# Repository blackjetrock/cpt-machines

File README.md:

# CPT Machine information

The CPT Corporation made a few word processor machines in the 1970s and 80s. There is information here about specifically the:

4200
8000
8500

CPT 4200
========

This is a TTL (no processor) word processing tool that used a (modified) IBM Selectric for input and output. The 4200 console was a unit with a few keys and two tape decks. Text could be saved on the tapes, together with information such as names and addresses, these could be combined automatically later, creating a mail-merge facility.

CPT8000
=======
The 8000 is an 8080 based word processing system. It uses floppy drives for storage.

CPT8500
=======

The 8500 is an 8000 in a condensed form. The circuitry from the 8000 has been squashed down onto a smaller number of PCBs.

8000 Re-creation
================

I have a set of CPT8500 PCBs, but nothing else. I'm planning on recreating the parts I need in order to get the boards running again.

The backplane is the first part needed, this has been designed and is untested:

I've also designed a diagnostic/debug card (untested) which is a Pico on a bus:

Acknowledgements
================

Thanks to Adrian at Binary Dinosaurs, who has helped a lot with data from his real CPT machine.
Rich, who used to work at CPT has generously scanned and supplied the chematics of the 8000, without which these projects would not have started.

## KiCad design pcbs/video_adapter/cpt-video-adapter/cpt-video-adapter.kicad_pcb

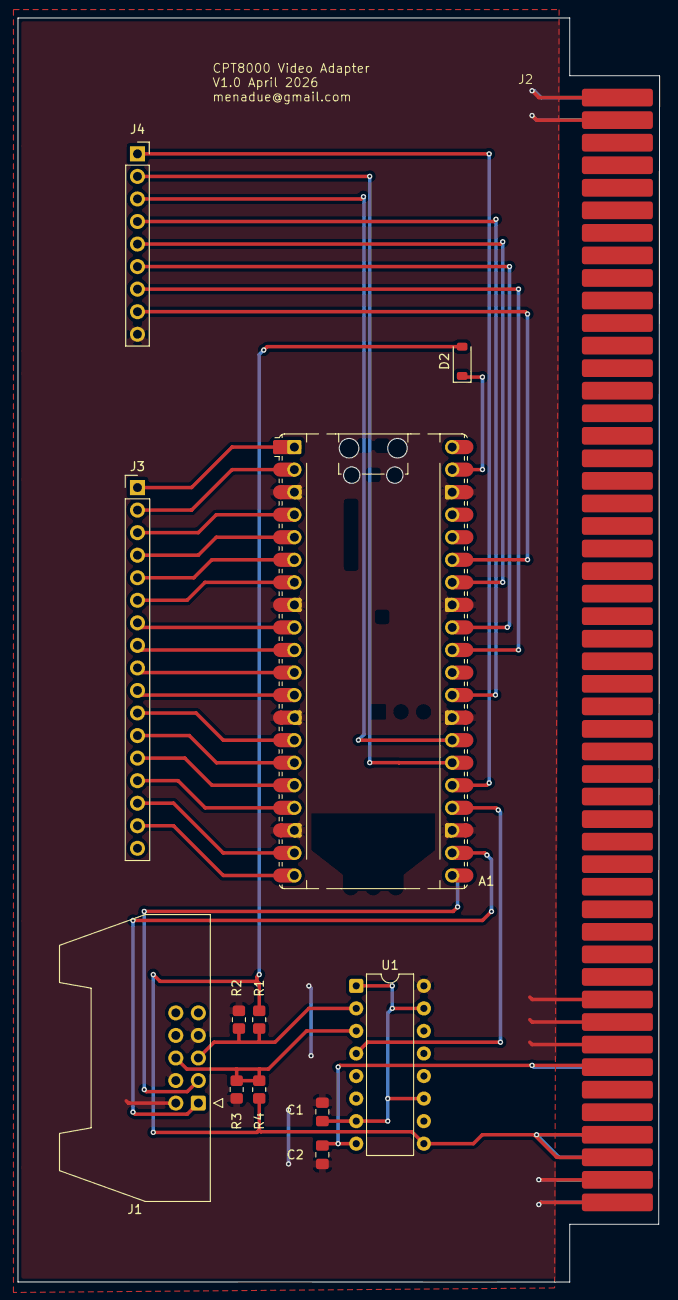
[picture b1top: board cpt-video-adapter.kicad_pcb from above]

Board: 2 copper layers, 72.3 x 142.4 mm, 13 parts (0 on the bottom side), 34 nets.

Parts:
A1: RaspberryPi_Pico; RaspberryPi_Pico_Common_Unspecified
C1, C2: C_Small; C_0805_2012Metric_Pad1.18x1.45mm_HandSolder
D2: D_Schottky; D_SOD-123
J1: Conn_02x05_Odd_Even; IDC-Header_2x05_P2.54mm_Latch_Horizontal
J2: cpt-backplane_100; cpt-card-edge-100
J3: Conn_01x17_Pin; PinHeader_1x17_P2.54mm_Vertical
J4: Conn_01x09; PinSocket_1x09_P2.54mm_Vertical
R1, R2, R3, R4: R_Small; R_0805_2012Metric_Pad1.20x1.40mm_HandSolder
U1: mc10125; DIP-16_W7.62mm

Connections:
+5V: D2.2 (A), J2.93 (+5V), J2.94 (+5V), J2.95 (+5V), J2.96 (+5V), R1.1, R3.1, U1.9 (VCC)
-5V: C2.1, J2.87 (-5V), J2.88 (-5V), U1.8 (VEE)
GND: A1.3 (GND), A1.8 (GND), A1.13 (GND), A1.18 (GND), A1.23 (GND), A1.28 (GND), A1.33 (AGND), A1.38 (GND), C1.2, C2.2, J1.2, J1.4, J1.7, J2.1 (GND), J2.2 (GND), J2.3 (GND), J2.4 (GND), J2.82 (GND), J2.84 (GND), J2.86 (GND), J2.97 (GND), J2.98 (GND), J2.99 (GND), J2.100 (GND), J4.9, R2.2, R4.2, U1.16 (GND)
HSYNC: A1.22 (GPIO17), J1.1
unnamed: A1.35 (ADC_VREF), J4.8
unnamed: A1.1 (GPIO0), J3.1
unnamed: A1.2 (GPIO1), J3.2
unnamed: A1.4 (GPIO2), J3.3
unnamed: A1.5 (GPIO3), J3.4
unnamed: A1.6 (GPIO4), J3.5
unnamed: A1.7 (GPIO5), J3.6
unnamed: A1.9 (GPIO6), J3.7
unnamed: A1.10 (GPIO7), J3.8
unnamed: A1.11 (GPIO8), J3.9
unnamed: A1.12 (GPIO9), J3.10
unnamed: A1.14 (GPIO10), J3.11
unnamed: A1.15 (GPIO11), J3.12
unnamed: A1.16 (GPIO12), J3.13
unnamed: A1.17 (GPIO13), J3.14
unnamed: A1.19 (GPIO14), J3.15
unnamed: A1.20 (GPIO15), J3.16
unnamed: A1.25 (GPIO19), J4.1
unnamed: A1.26 (GPIO20), J4.2
unnamed: A1.27 (GPIO21), J4.3
unnamed: A1.29 (GPIO22), J4.4
unnamed: A1.31 (GPIO26_ADC0), J4.7
unnamed: A1.32 (GPIO27_ADC1), J4.6
unnamed: A1.34 (GPIO28_ADC2), J4.5
unnamed: A1.39 (VSYS), D2.1 (K)
unnamed: C1.1, U1.1 (VBB), U1.7 (BIN), U1.11 (CIN), U1.15 (DIN)
VIDEO_N: J1.5, R1.2, R2.1, U1.2 (/AIN)
VIDEO_P: J1.6, R3.2, R4.1, U1.3 (AIN)
VIDEO_TTL: A1.24 (GPIO18), U1.4 (AOUT)
VSYNC: A1.21 (GPIO16), J1.3

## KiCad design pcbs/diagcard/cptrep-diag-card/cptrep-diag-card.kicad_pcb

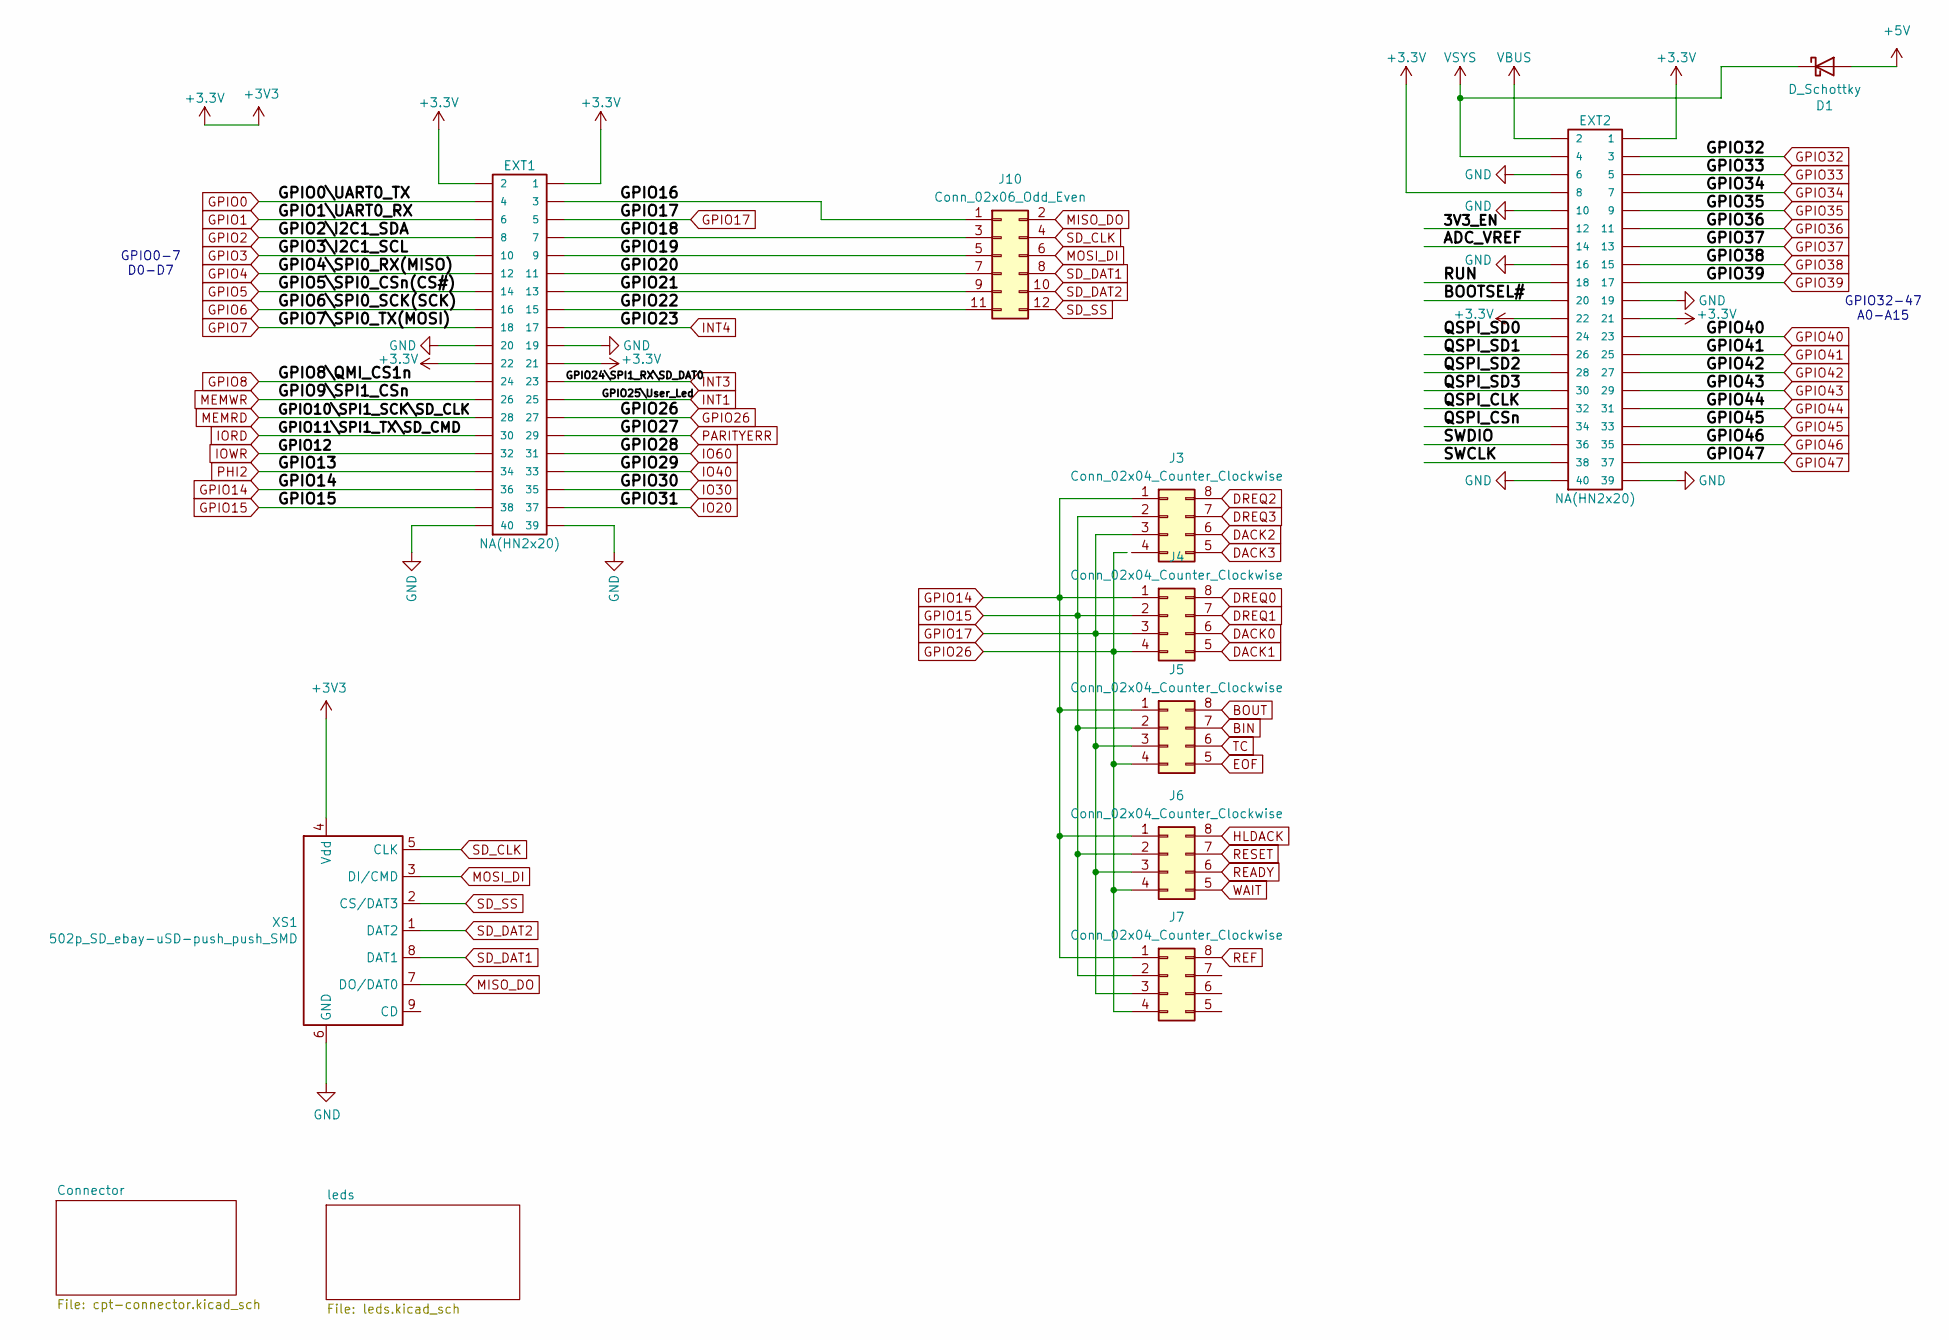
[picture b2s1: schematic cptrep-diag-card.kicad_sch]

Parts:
D1: D_Schottky; D_SOD-123
EXT1, EXT2: NA(HN2x20); PinSocket_2x20_P2.54mm_Vertical
J3, J4, J5, J6, J7: Conn_02x04_Counter_Clockwise; PinHeader_2x04_P2.54mm_Vertical
J10: Conn_02x06_Odd_Even; PinHeader_2x06_P2.54mm_Vertical
XS1: 502p_SD_ebay-uSD-push_push_SMD; Conn_uSDcard

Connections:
+3.3V: EXT1.1, EXT1.2, EXT1.21, EXT1.22, EXT2.1, EXT2.8, EXT2.21, EXT2.22, XS1.4 (Vdd)
+5V: D1.2 (A); also elsewhere on the board
/3V3_EN: EXT2.12
/ADC_VREF: EXT2.14
/BOOTSEL#: EXT2.20
/GPIO16: EXT1.3, J10.1
/GPIO18: EXT1.7, J10.3
/GPIO19: EXT1.9, J10.5
/GPIO20: EXT1.11, J10.7
/GPIO21: EXT1.13, J10.9
/GPIO22: EXT1.15, J10.11
/QSPI_CLK: EXT2.32
/QSPI_CSn: EXT2.34
/QSPI_SD0: EXT2.24
/QSPI_SD1: EXT2.26
/QSPI_SD2: EXT2.28
/QSPI_SD3: EXT2.30
/RUN: EXT2.18
/SWCLK: EXT2.38
/SWDIO: EXT2.36
BIN: J5.7; also elsewhere on the board
BOUT: J5.8; also elsewhere on the board
DACK0: J4.6; also elsewhere on the board
DACK1: J4.5; also elsewhere on the board
DACK2: J3.6; also elsewhere on the board
DACK3: J3.5; also elsewhere on the board
DREQ0: J4.8; also elsewhere on the board
DREQ1: J4.7; also elsewhere on the board
DREQ2: J3.8; also elsewhere on the board
DREQ3: J3.7; also elsewhere on the board
EOF: J5.5; also elsewhere on the board
GND: EXT1.19, EXT1.20, EXT1.39, EXT1.40, EXT2.6, EXT2.10, EXT2.16, EXT2.19, EXT2.39, EXT2.40, XS1.6 (GND); also elsewhere on the board
GPIO0: EXT1.4; also elsewhere on the board
GPIO1: EXT1.6; also elsewhere on the board
GPIO2: EXT1.8; also elsewhere on the board
GPIO3: EXT1.10; also elsewhere on the board
GPIO4: EXT1.12; also elsewhere on the board
GPIO5: EXT1.14; also elsewhere on the board
GPIO6: EXT1.16; also elsewhere on the board
GPIO7: EXT1.18; also elsewhere on the board
GPIO8: EXT1.24; also elsewhere on the board
GPIO14: EXT1.36, J3.1, J4.1, J5.1, J6.1, J7.1; also elsewhere on the board
GPIO15: EXT1.38, J3.2, J4.2, J5.2, J6.2, J7.2; also elsewhere on the board
GPIO17: EXT1.5, J3.3, J4.3, J5.3, J6.3, J7.3; also elsewhere on the board
GPIO26: EXT1.27, J4.4, J5.4, J6.4, J7.4; also elsewhere on the board
GPIO32: EXT2.3; also elsewhere on the board
GPIO33: EXT2.5; also elsewhere on the board
GPIO34: EXT2.7; also elsewhere on the board
GPIO35: EXT2.9; also elsewhere on the board
GPIO36: EXT2.11; also elsewhere on the board
GPIO37: EXT2.13; also elsewhere on the board
GPIO38: EXT2.15; also elsewhere on the board
GPIO39: EXT2.17; also elsewhere on the board
GPIO40: EXT2.23; also elsewhere on the board
GPIO41: EXT2.25; also elsewhere on the board
GPIO42: EXT2.27; also elsewhere on the board
GPIO43: EXT2.29; also elsewhere on the board
GPIO44: EXT2.31; also elsewhere on the board
GPIO45: EXT2.33; also elsewhere on the board
GPIO46: EXT2.35; also elsewhere on the board
GPIO47: EXT2.37; also elsewhere on the board
HLDACK: J6.8; also elsewhere on the board
INT1: EXT1.25; also elsewhere on the board
INT3: EXT1.23; also elsewhere on the board
INT4: EXT1.17; also elsewhere on the board
IO20: EXT1.37; also elsewhere on the board
IO30: EXT1.35; also elsewhere on the board
IO40: EXT1.33; also elsewhere on the board
IO60: EXT1.31; also elsewhere on the board
IORD: EXT1.30; also elsewhere on the board
IOWR: EXT1.32; also elsewhere on the board
MEMRD: EXT1.28; also elsewhere on the board
MEMWR: EXT1.26; also elsewhere on the board
MISO_DO: J10.2, XS1.7 (DO/DAT0)
MOSI_DI: J10.6, XS1.3 (DI/CMD)
PARITYERR: EXT1.29; also elsewhere on the board
PHI2: EXT1.34; also elsewhere on the board
READY: J6.6; also elsewhere on the board
REF: J7.8; also elsewhere on the board
RESET: J6.7; also elsewhere on the board
SD_CLK: J10.4, XS1.5 (CLK)
SD_DAT1: J10.8, XS1.8 (DAT1)
SD_DAT2: J10.10, XS1.1 (DAT2)
SD_SS: J10.12, XS1.2 (CS/DAT3)
TC: J5.6; also elsewhere on the board
VBUS: EXT2.2
VSYS: D1.1 (K), EXT2.4
WAIT: J6.5; also elsewhere on the board

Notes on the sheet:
GPIO32-47 A0-A15
GPIO0-7 D0-D7

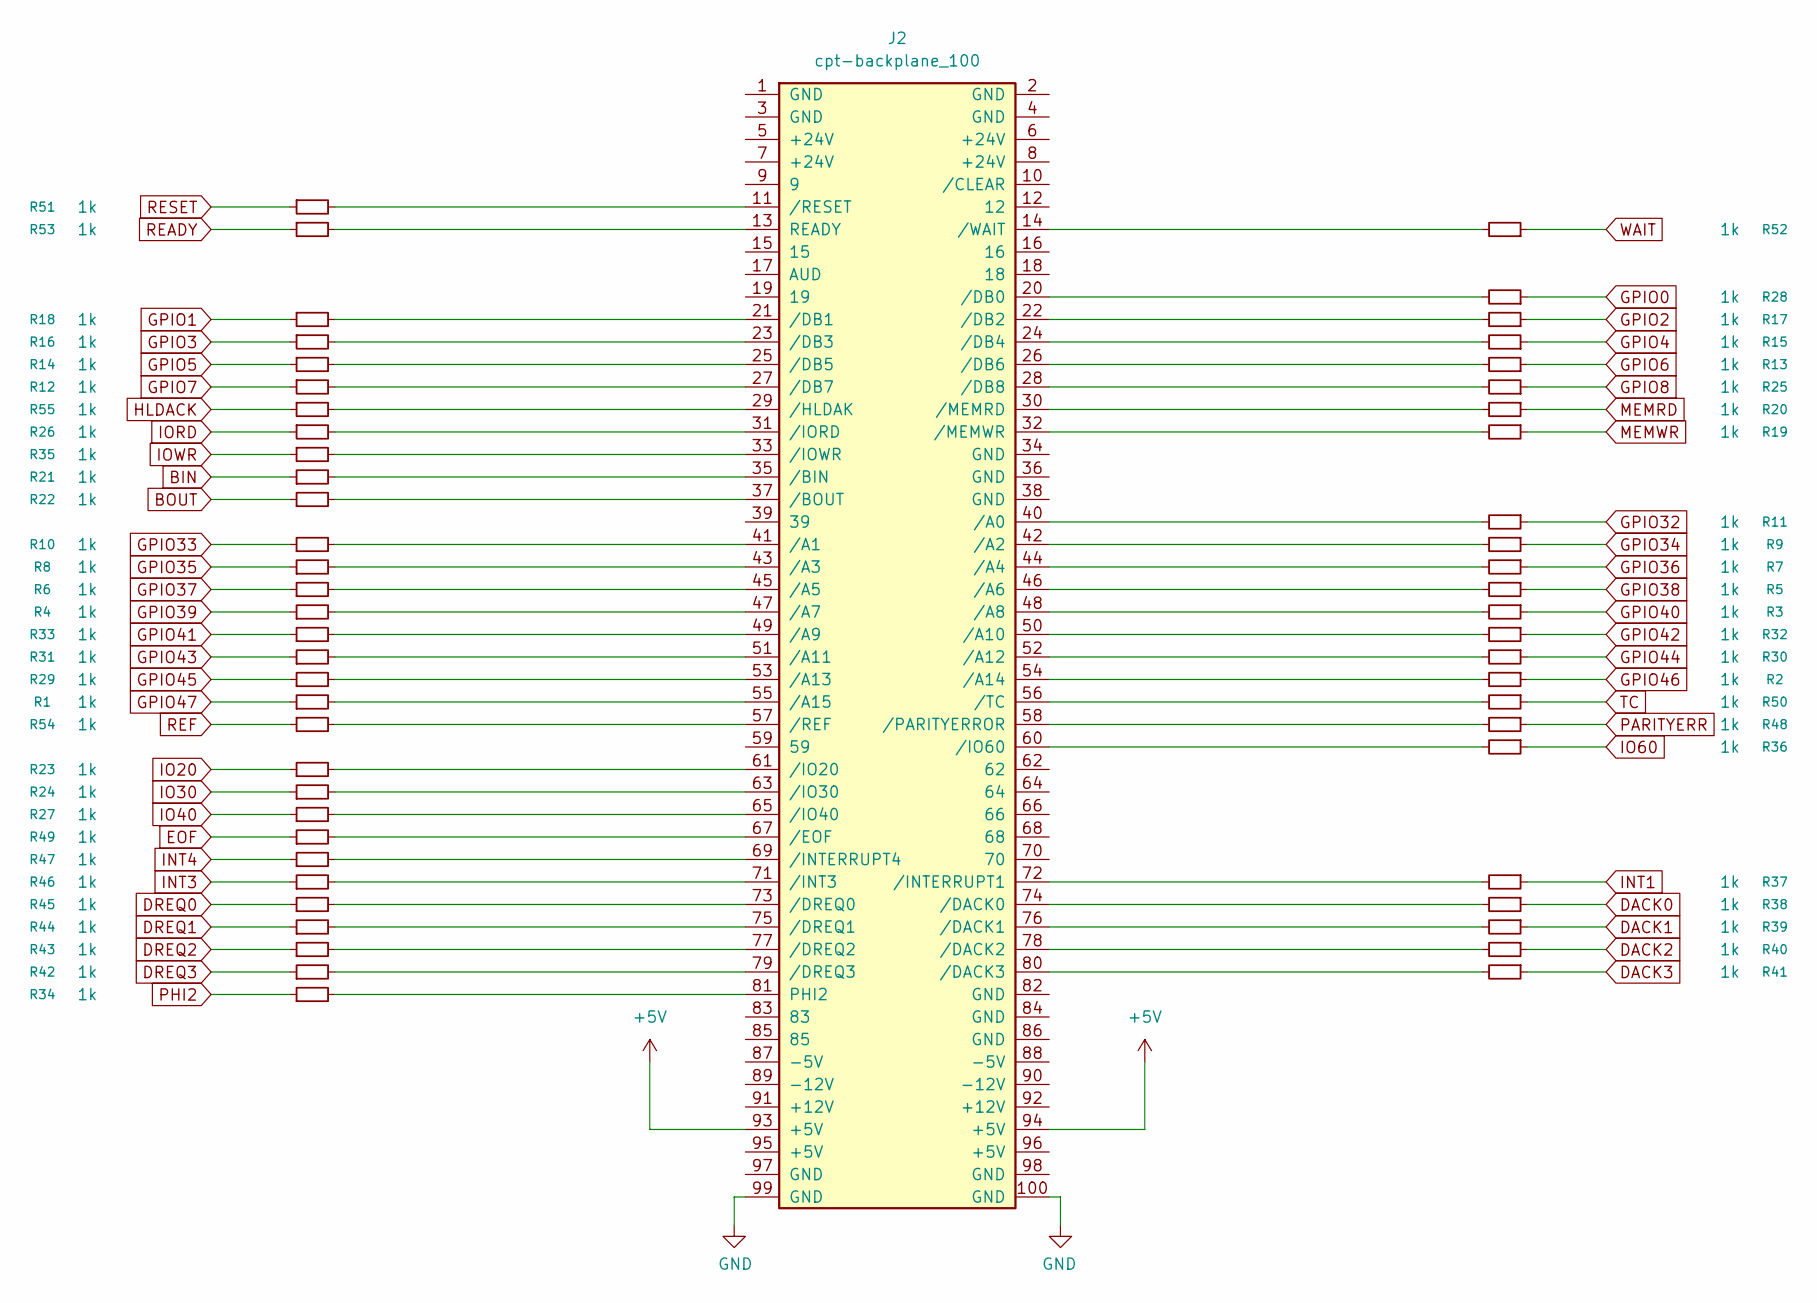
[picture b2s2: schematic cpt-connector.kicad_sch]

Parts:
J2: cpt-backplane_100; cpt-card-edge-100
R1, R2, R3, R4, R5, R6, R7, R8, R9, R10, R11, R12, R13, R14, R15, R16, R17, R18, R19, R20, R21, R22, R23, R24, R25, R26, R27, R28, R29, R30, R31, R32, R33, R34, R35, R36, R37, R38, R39, R40, R41, R42, R43, R44, R45, R46, R47, R48, R49, R50, R51, R52, R53, R54, R55: 1k; R_0805_2012Metric_Pad1.20x1.40mm_HandSolder

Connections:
+5V: J2.93 (+5V), J2.94 (+5V); also elsewhere on the board
BIN: R21.1; also elsewhere on the board
BOUT: R22.1; also elsewhere on the board
DACK0: R38.1; also elsewhere on the board
DACK1: R39.1; also elsewhere on the board
DACK2: R40.1; also elsewhere on the board
DACK3: R41.1; also elsewhere on the board
DREQ0: R45.1; also elsewhere on the board
DREQ1: R44.1; also elsewhere on the board
DREQ2: R43.1; also elsewhere on the board
DREQ3: R42.1; also elsewhere on the board
EOF: R49.1; also elsewhere on the board
GND: J2.1 (GND), J2.2 (GND), J2.3 (GND), J2.4 (GND), J2.99 (GND), J2.100 (GND); also elsewhere on the board
GPIO0: R28.1; also elsewhere on the board
GPIO1: R18.1; also elsewhere on the board
GPIO2: R17.1; also elsewhere on the board
GPIO3: R16.1; also elsewhere on the board
GPIO4: R15.1; also elsewhere on the board
GPIO5: R14.1; also elsewhere on the board
GPIO6: R13.1; also elsewhere on the board
GPIO7: R12.1; also elsewhere on the board
GPIO8: R25.1; also elsewhere on the board
GPIO32: R11.1; also elsewhere on the board
GPIO33: R10.1; also elsewhere on the board
GPIO34: R9.1; also elsewhere on the board
GPIO35: R8.1; also elsewhere on the board
GPIO36: R7.1; also elsewhere on the board
GPIO37: R6.1; also elsewhere on the board
GPIO38: R5.1; also elsewhere on the board
GPIO39: R4.1; also elsewhere on the board
GPIO40: R3.1; also elsewhere on the board
GPIO41: R33.1; also elsewhere on the board
GPIO42: R32.1; also elsewhere on the board
GPIO43: R31.1; also elsewhere on the board
GPIO44: R30.1; also elsewhere on the board
GPIO45: R29.1; also elsewhere on the board
GPIO46: R2.1; also elsewhere on the board
GPIO47: R1.1; also elsewhere on the board
HLDACK: R55.1; also elsewhere on the board
INT1: R37.1; also elsewhere on the board
INT3: R46.1; also elsewhere on the board
INT4: R47.1; also elsewhere on the board
IO20: R23.1; also elsewhere on the board
IO30: R24.1; also elsewhere on the board
IO40: R27.1; also elsewhere on the board
IO60: R36.1; also elsewhere on the board
IORD: R26.1; also elsewhere on the board
IOWR: R35.1; also elsewhere on the board
MEMRD: R20.1; also elsewhere on the board
MEMWR: R19.1; also elsewhere on the board
unnamed: J2.81 (PHI2), R34.2
unnamed: J2.13 (READY), R53.2
unnamed: J2.40 (/A0), R11.2
unnamed: J2.41 (/A1), R10.2
unnamed: J2.42 (/A2), R9.2
unnamed: J2.43 (/A3), R8.2
unnamed: J2.44 (/A4), R7.2
unnamed: J2.45 (/A5), R6.2
unnamed: J2.46 (/A6), R5.2
unnamed: J2.47 (/A7), R4.2
unnamed: J2.48 (/A8), R3.2
unnamed: J2.49 (/A9), R33.2
unnamed: J2.50 (/A10), R32.2
unnamed: J2.51 (/A11), R31.2
unnamed: J2.52 (/A12), R30.2
unnamed: J2.53 (/A13), R29.2
unnamed: J2.54 (/A14), R2.2
unnamed: J2.55 (/A15), R1.2
unnamed: J2.35 (/BIN), R21.2
unnamed: J2.37 (/BOUT), R22.2
unnamed: J2.74 (/DACK0), R38.2
unnamed: J2.76 (/DACK1), R39.2
unnamed: J2.78 (/DACK2), R40.2
unnamed: J2.80 (/DACK3), R41.2
unnamed: J2.20 (/DB0), R28.2
unnamed: J2.21 (/DB1), R18.2
unnamed: J2.22 (/DB2), R17.2
unnamed: J2.23 (/DB3), R16.2
unnamed: J2.24 (/DB4), R15.2
unnamed: J2.25 (/DB5), R14.2
unnamed: J2.26 (/DB6), R13.2
unnamed: J2.27 (/DB7), R12.2
unnamed: J2.28 (/DB8), R25.2
unnamed: J2.73 (/DREQ0), R45.2
unnamed: J2.75 (/DREQ1), R44.2
unnamed: J2.77 (/DREQ2), R43.2
unnamed: J2.79 (/DREQ3), R42.2
unnamed: J2.67 (/EOF), R49.2
unnamed: J2.29 (/HLDAK), R55.2
unnamed: J2.71 (/INT3), R46.2
unnamed: J2.72 (/INTERRUPT1), R37.2
unnamed: J2.69 (/INTERRUPT4), R47.2
unnamed: J2.61 (/IO20), R23.2
unnamed: J2.63 (/IO30), R24.2
unnamed: J2.65 (/IO40), R27.2
unnamed: J2.60 (/IO60), R36.2
unnamed: J2.31 (/IORD), R26.2
unnamed: J2.33 (/IOWR), R35.2
unnamed: J2.30 (/MEMRD), R20.2
unnamed: J2.32 (/MEMWR), R19.2
unnamed: J2.58 (/PARITYERROR), R48.2
unnamed: J2.57 (/REF), R54.2
unnamed: J2.11 (/RESET), R51.2
unnamed: J2.56 (/TC), R50.2
unnamed: J2.14 (/WAIT), R52.2
PARITYERR: R48.1; also elsewhere on the board
PHI2: R34.1; also elsewhere on the board
READY: R53.1; also elsewhere on the board
REF: R54.1; also elsewhere on the board
RESET: R51.1; also elsewhere on the board
TC: R50.1; also elsewhere on the board
WAIT: R52.1; also elsewhere on the board

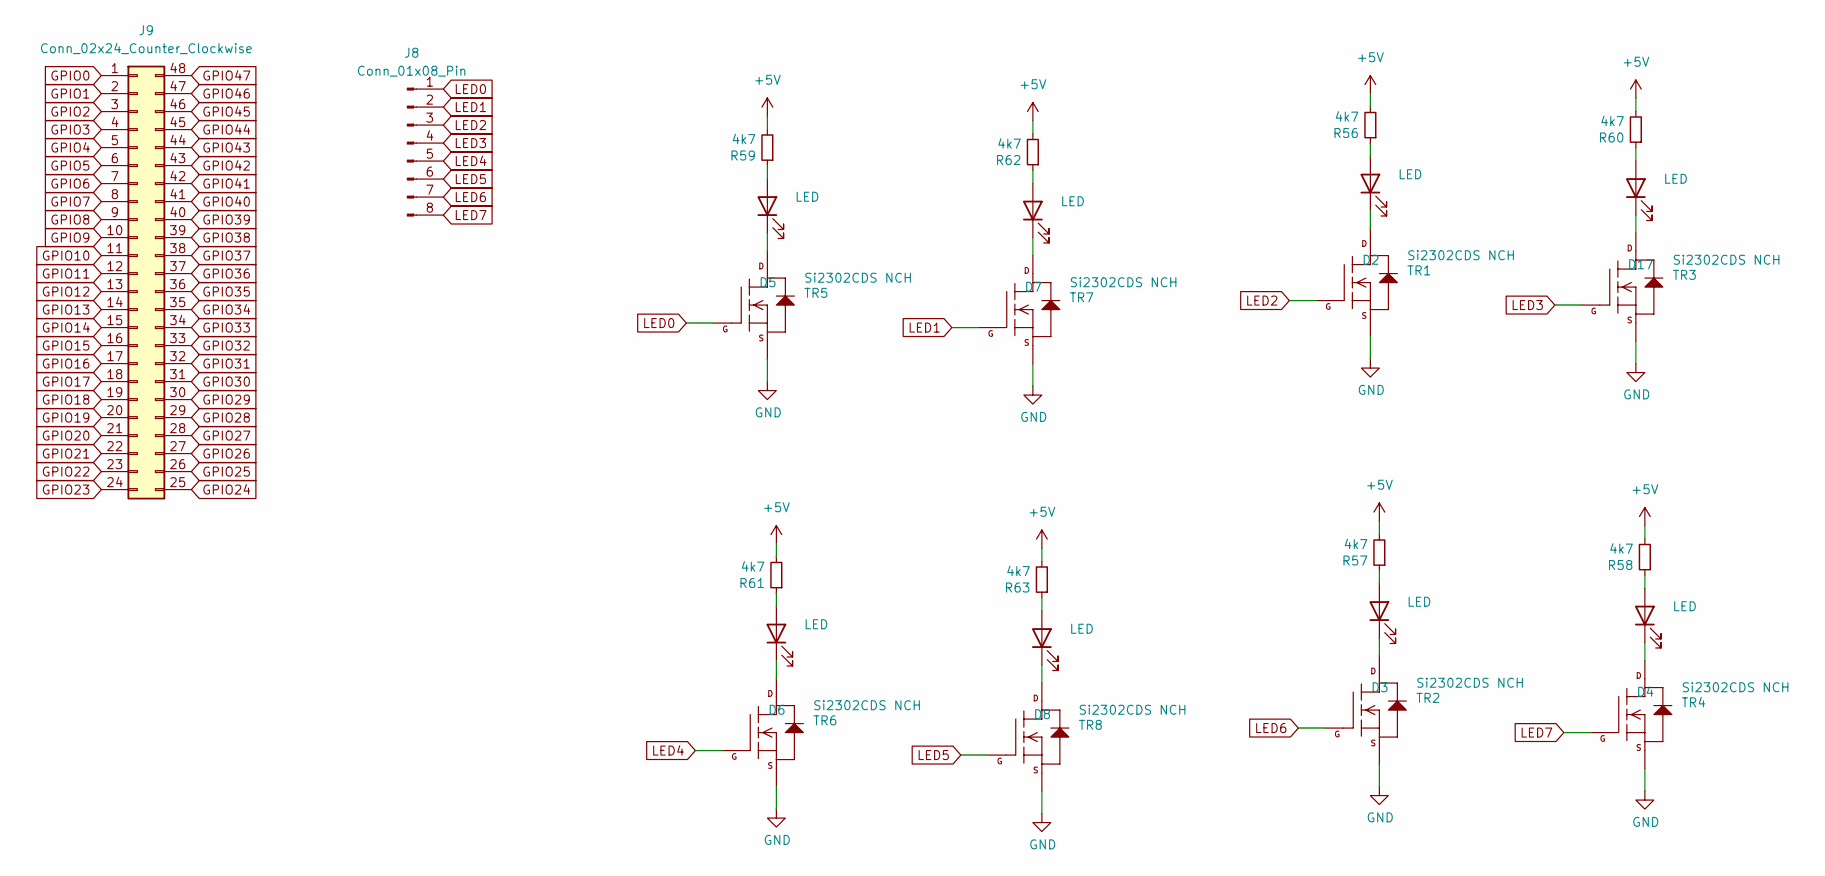
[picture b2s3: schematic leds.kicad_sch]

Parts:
D2, D3, D4, D5, D6, D7, D8, D17: LED; LED_0805_2012Metric
J8: Conn_01x08_Pin; PinHeader_1x08_P2.54mm_Vertical
J9: Conn_02x24_Counter_Clockwise; PinHeader_2x24_P2.54mm_Vertical
R56, R57, R58, R59, R60, R61, R62, R63: 4k7; R_0805_2012Metric
TR1, TR2, TR3, TR4, TR5, TR6, TR7, TR8: Si2302CDS NCH; SOT-23

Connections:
+5V: R56.2, R57.2, R58.2, R59.2, R60.2, R61.2, R62.2, R63.2; also elsewhere on the board
GND: TR1.2 (S), TR2.2 (S), TR3.2 (S), TR4.2 (S), TR5.2 (S), TR6.2 (S), TR7.2 (S), TR8.2 (S); also elsewhere on the board
GPIO0: J9.1; also elsewhere on the board
GPIO1: J9.2; also elsewhere on the board
GPIO2: J9.3; also elsewhere on the board
GPIO3: J9.4; also elsewhere on the board
GPIO4: J9.5; also elsewhere on the board
GPIO5: J9.6; also elsewhere on the board
GPIO6: J9.7; also elsewhere on the board
GPIO7: J9.8; also elsewhere on the board
GPIO8: J9.9; also elsewhere on the board
GPIO9: J9.10
GPIO10: J9.11
GPIO11: J9.12
GPIO12: J9.13
GPIO13: J9.14
GPIO14: J9.15; also elsewhere on the board
GPIO15: J9.16; also elsewhere on the board
GPIO16: J9.17
GPIO17: J9.18; also elsewhere on the board
GPIO18: J9.19
GPIO19: J9.20
GPIO20: J9.21
GPIO21: J9.22
GPIO22: J9.23
GPIO23: J9.24
GPIO24: J9.25
GPIO25: J9.26
GPIO26: J9.27; also elsewhere on the board
GPIO27: J9.28
GPIO28: J9.29
GPIO29: J9.30
GPIO30: J9.31
GPIO31: J9.32
GPIO32: J9.33; also elsewhere on the board
GPIO33: J9.34; also elsewhere on the board
GPIO34: J9.35; also elsewhere on the board
GPIO35: J9.36; also elsewhere on the board
GPIO36: J9.37; also elsewhere on the board
GPIO37: J9.38; also elsewhere on the board
GPIO38: J9.39; also elsewhere on the board
GPIO39: J9.40; also elsewhere on the board
GPIO40: J9.41; also elsewhere on the board
GPIO41: J9.42; also elsewhere on the board
GPIO42: J9.43; also elsewhere on the board
GPIO43: J9.44; also elsewhere on the board
GPIO44: J9.45; also elsewhere on the board
GPIO45: J9.46; also elsewhere on the board
GPIO46: J9.47; also elsewhere on the board
GPIO47: J9.48; also elsewhere on the board
LED0: J8.1, TR5.1 (G)
LED1: J8.2, TR7.1 (G)
LED2: J8.3, TR1.1 (G)
LED3: J8.4, TR3.1 (G)
LED4: J8.5, TR6.1 (G)
LED5: J8.6, TR8.1 (G)
LED6: J8.7, TR2.1 (G)
LED7: J8.8, TR4.1 (G)
unnamed: D2.2 (A), R56.1
unnamed: D2.1 (K), TR1.3 (D)
unnamed: D3.2 (A), R57.1
unnamed: D3.1 (K), TR2.3 (D)
unnamed: D4.2 (A), R58.1
unnamed: D4.1 (K), TR4.3 (D)
unnamed: D5.2 (A), R59.1
unnamed: D5.1 (K), TR5.3 (D)
unnamed: D6.2 (A), R61.1
unnamed: D6.1 (K), TR6.3 (D)
unnamed: D7.2 (A), R62.1
unnamed: D7.1 (K), TR7.3 (D)
unnamed: D8.2 (A), R63.1
unnamed: D8.1 (K), TR8.3 (D)
unnamed: D17.2 (A), R60.1
unnamed: D17.1 (K), TR3.3 (D)

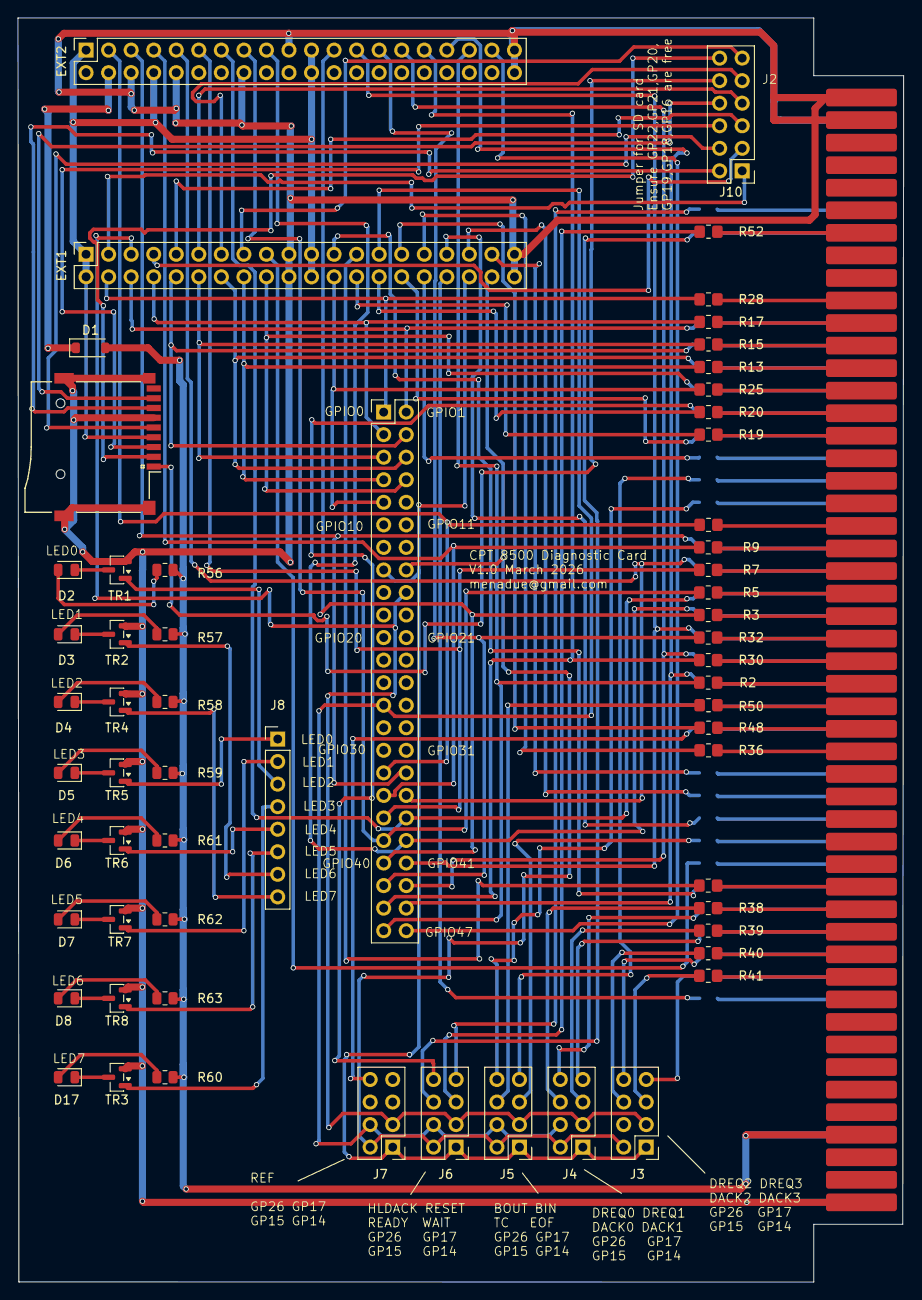
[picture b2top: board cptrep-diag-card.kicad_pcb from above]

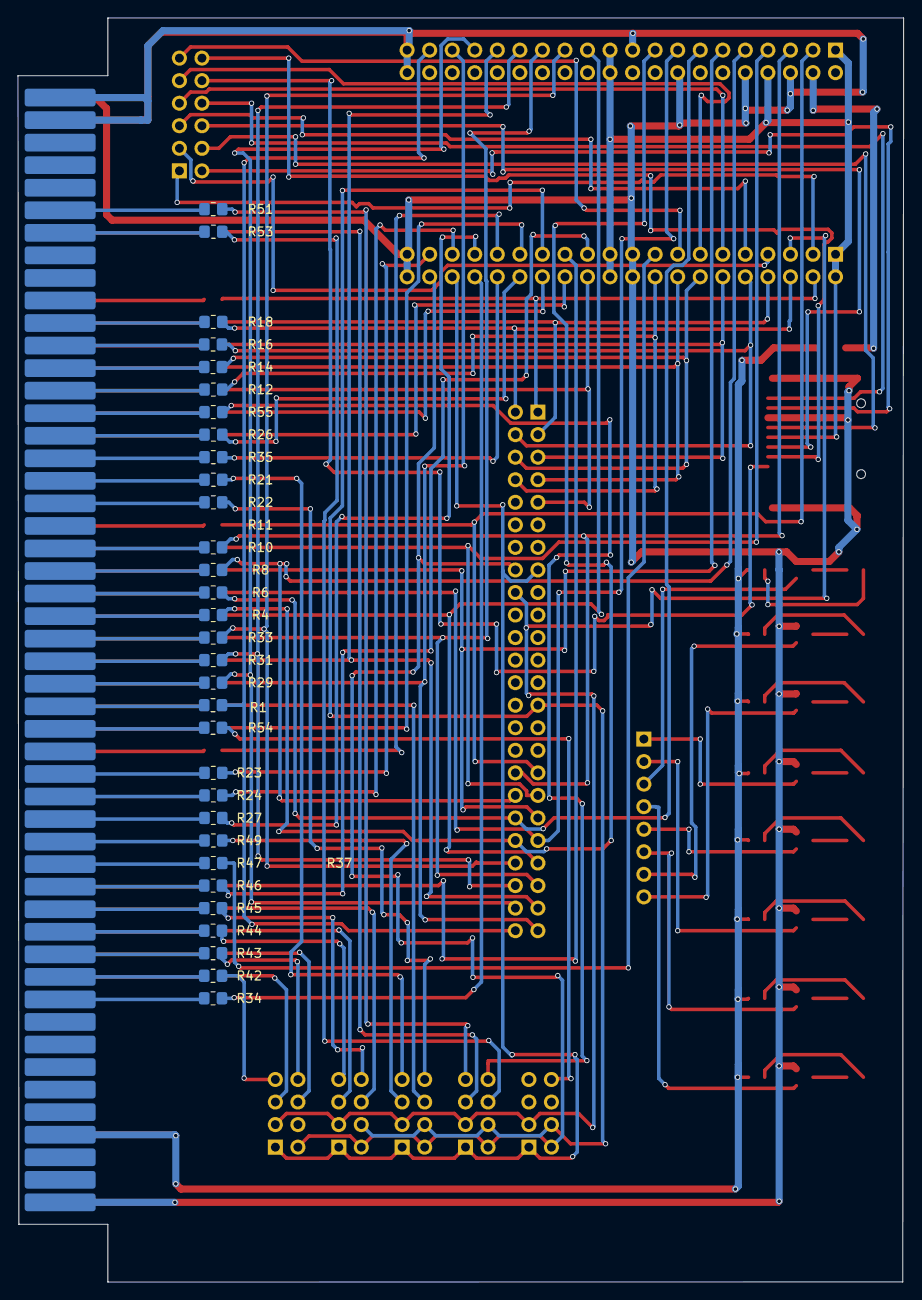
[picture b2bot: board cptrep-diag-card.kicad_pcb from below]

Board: 2 copper layers, 99.8 x 142.4 mm, 92 parts (31 on the bottom side), 154 nets.

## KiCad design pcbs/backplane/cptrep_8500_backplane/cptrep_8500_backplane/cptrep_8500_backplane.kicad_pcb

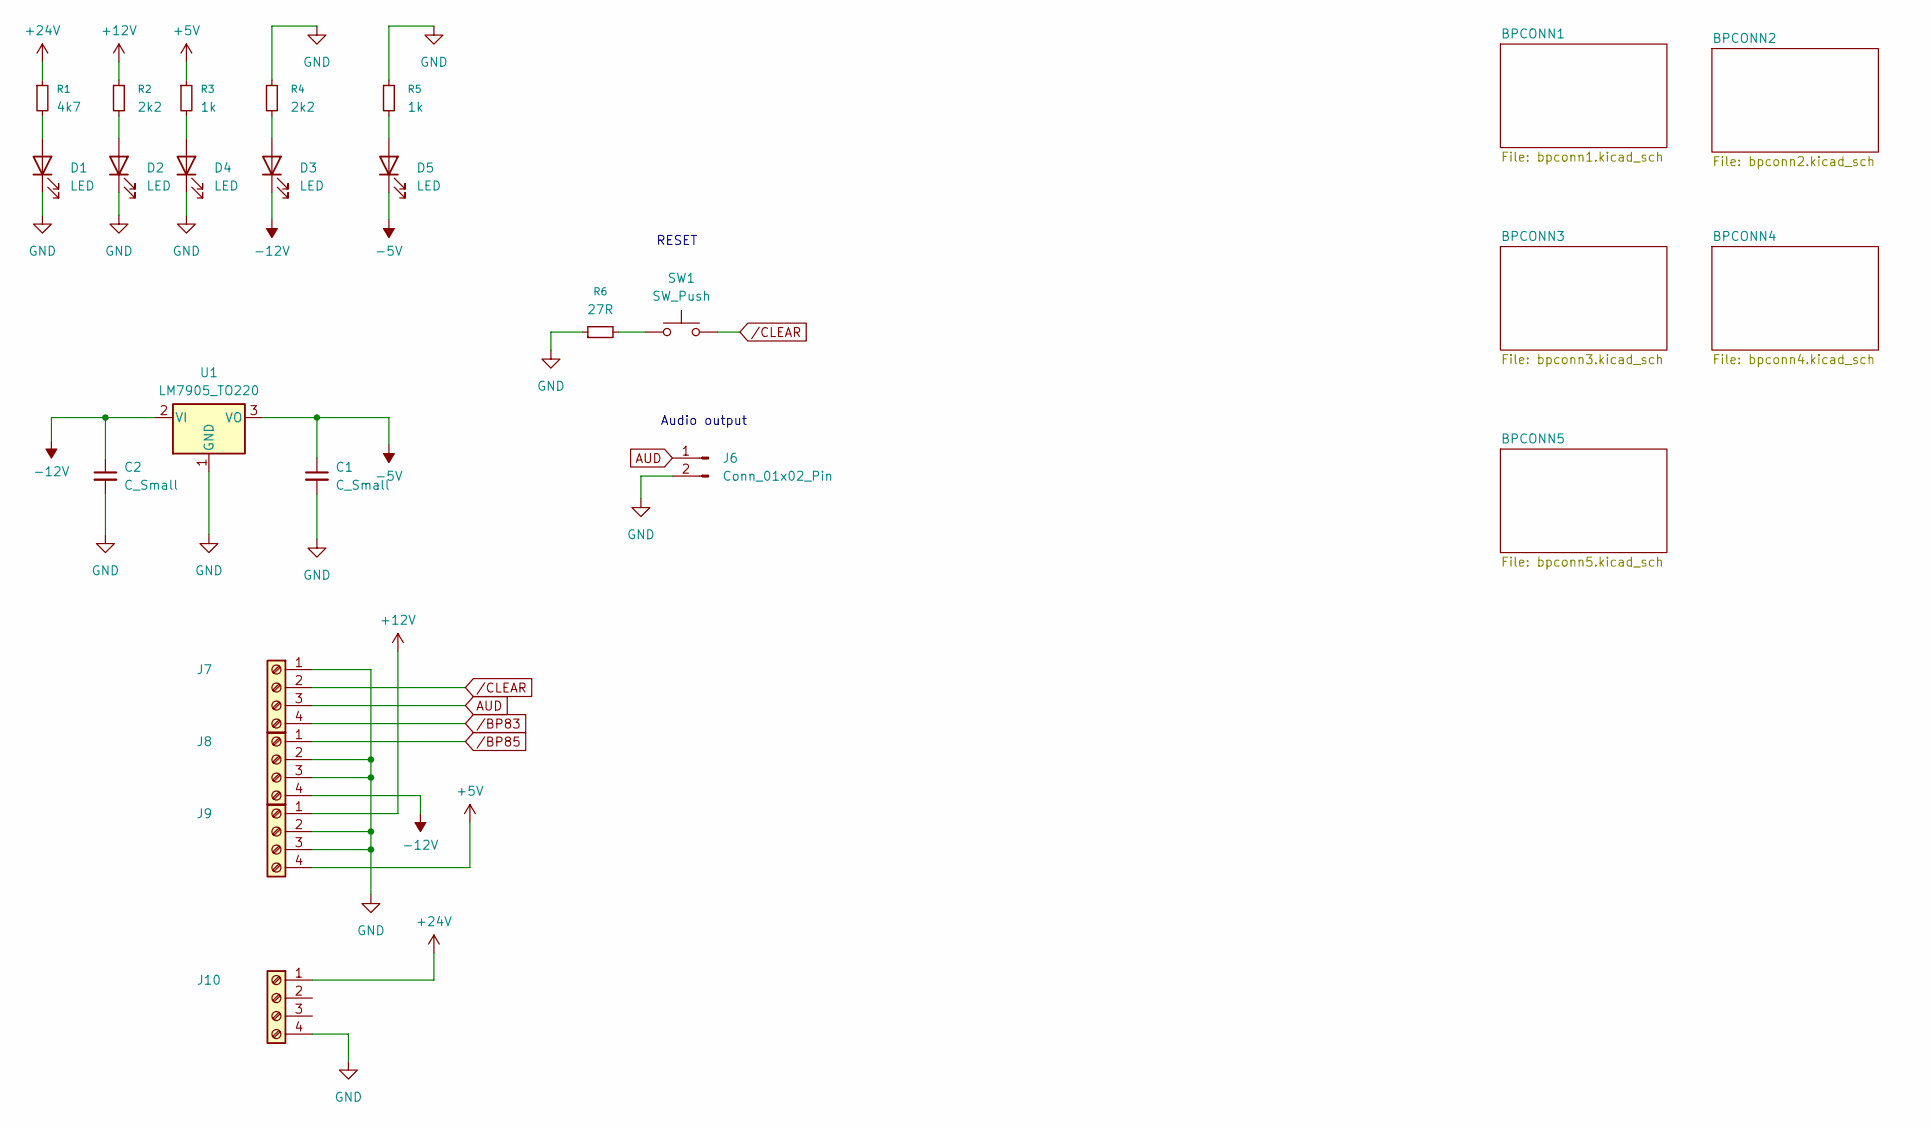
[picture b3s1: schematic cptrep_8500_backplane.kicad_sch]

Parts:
C1, C2: C_Small; C_0805_2012Metric_Pad1.18x1.45mm_HandSolder
D1, D2, D3, D4, D5: LED; LED_0805_2012Metric_Pad1.15x1.40mm_HandSolder
J6: Conn_01x02_Pin; PinSocket_1x02_P2.54mm_Vertical
J7, J8, J9, J10: Screw_Terminal_01x04; TerminalBlock_Phoenix_MKDS-1,5-4_1x04_P5.00mm_Horizontal
R1: 4k7; R_0805_2012Metric_Pad1.20x1.40mm_HandSolder
R2, R4: 2k2; R_0805_2012Metric_Pad1.20x1.40mm_HandSolder
R3, R5: 1k; R_0805_2012Metric_Pad1.20x1.40mm_HandSolder
R6: 27R; R_0805_2012Metric_Pad1.20x1.40mm_HandSolder
SW1: SW_Push; SW_PUSH_6mm
U1: LM7905_TO220; TO-220-3_Horizontal_TabDown

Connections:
+5V: J9.4, R3.1; also elsewhere on the board
+12V: J9.1, R2.1; also elsewhere on the board
+24V: J10.1, R1.1; also elsewhere on the board
-5V: C1.1, D5.1 (K), U1.3 (VO); also elsewhere on the board
-12V: C2.1, D3.1 (K), J8.4, U1.2 (VI); also elsewhere on the board
AUD: J6.1, J7.3; also elsewhere on the board
GND: C1.2, C2.2, D1.1 (K), D2.1 (K), D4.1 (K), J6.2, J7.1, J8.2, J8.3, J9.2, J9.3, J10.4, R4.1, R5.1, R6.1, U1.1 (GND); also elsewhere on the board
unnamed: D1.2 (A), R1.2
unnamed: D2.2 (A), R2.2
unnamed: D3.2 (A), R4.2
unnamed: D4.2 (A), R3.2
unnamed: D5.2 (A), R5.2
unnamed: R6.2, SW1.1
/BP83: J7.4; also elsewhere on the board
/BP85: J8.1; also elsewhere on the board
/CLEAR: J7.2, SW1.2; also elsewhere on the board

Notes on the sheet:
RESET
Audio output
